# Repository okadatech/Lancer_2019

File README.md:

# Lancer_2019
第22回ロボットグランプリ ランサー部門の機体データ

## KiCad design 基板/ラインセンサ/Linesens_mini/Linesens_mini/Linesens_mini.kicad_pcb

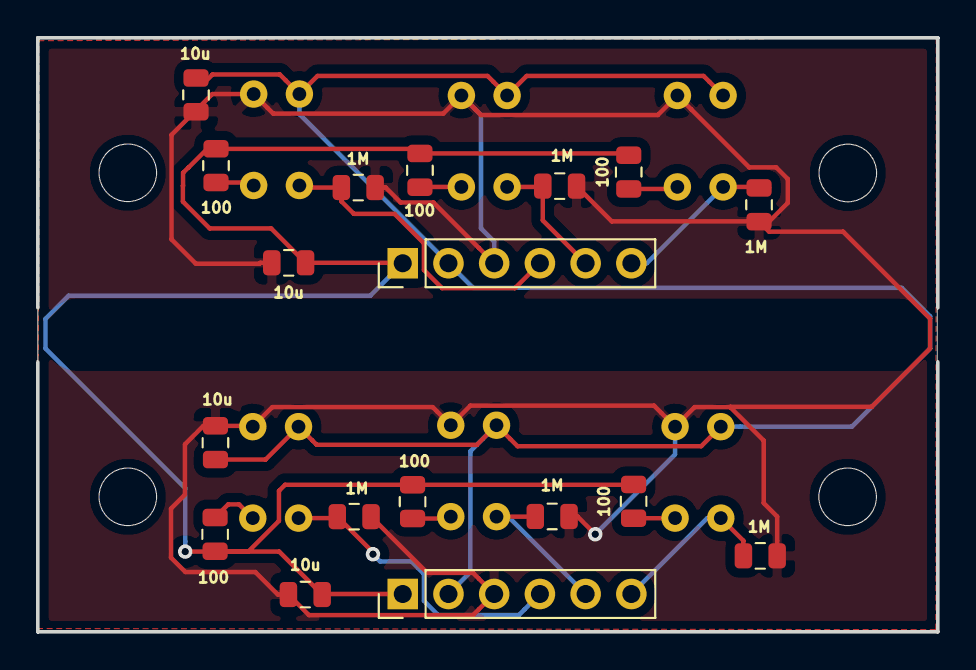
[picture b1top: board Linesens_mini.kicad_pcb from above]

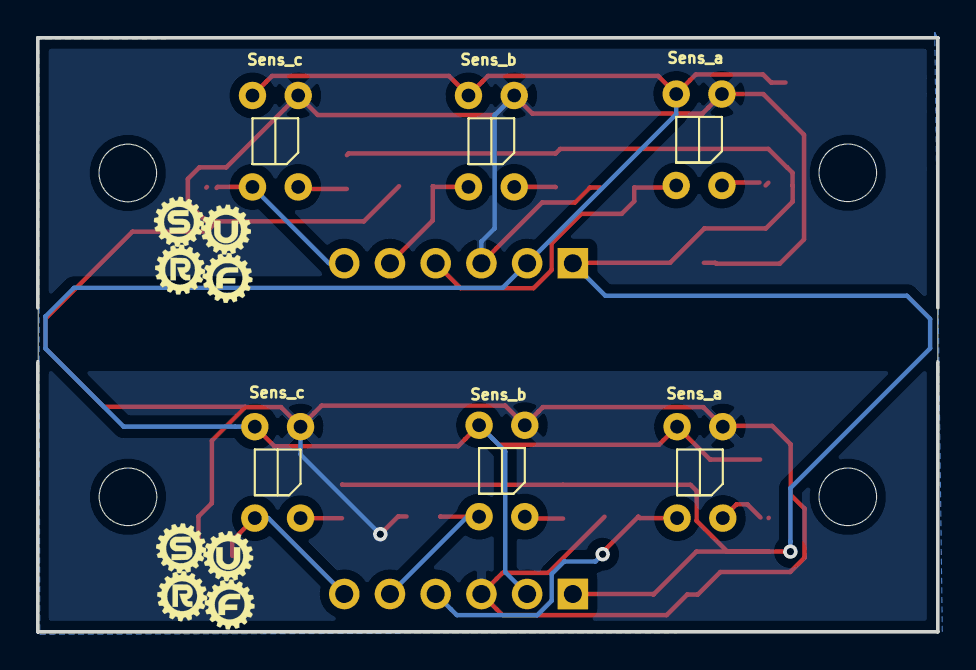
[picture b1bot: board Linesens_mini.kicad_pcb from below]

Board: 2 copper layers, 50.0 x 33.0 mm, 28 parts (6 on the bottom side), 15 nets.

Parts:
10u: 10u; C_0805_2012Metric
 : MountingHole_3.2mm_M3
 #2,  #3,  #6: MountingHole_3.2mm_M3
 #4,  #5: PinHeader_1x06_P2.54mm_Vertical
C1, C2, C4: 10u; C_0805_2012Metric
R1, R3, R5, R7, R9, R11: 100; R_0805_2012Metric
R2, R4, R6, R8, R10, R12: 1M; R_0805_2012Metric
Sens_a: TPR-105F
Sens_a#2: TPR-105F
Sens_b: TPR-105F
Sens_b#2: TPR-105F
Sens_c: TPR-105F
Sens_c#2: TPR-105F

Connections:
+3V3: #4.2, #5.2, C2.1, C4.1, Sens_a.3, Sens_a#2.3, Sens_b.3, Sens_b#2.3, Sens_c.3, Sens_c#2.3
+5V: 10u.1, #4.1, #5.1, C1.1, R1.1, R3.1, R5.1, R7.1, R9.1, R11.1
/Line_out_1: #4.6, R2.1, Sens_c.4
/Line_out_2: #4.5, R4.1, Sens_b.4
/Line_out_3: #4.4, R6.1, Sens_a#2.4
/Line_out_4: #5.6, R8.1, Sens_c#2.4
/Line_out_5: #5.5, R10.1, Sens_b#2.4
/Line_out_6: #5.4, R12.1, Sens_a.4
GND: 10u.2, #4.3, #5.3, C1.2, C2.2, C4.2, R2.2, R4.2, R6.2, R8.2, R10.2, R12.2, Sens_a.2, Sens_a#2.2, Sens_b.2, Sens_b#2.2, Sens_c.2, Sens_c#2.2
unnamed: R1.2, Sens_c.1
unnamed: R3.2, Sens_b.1
unnamed: R5.2, Sens_a#2.1
unnamed: R7.2, Sens_c#2.1
unnamed: R9.2, Sens_b#2.1
unnamed: R11.2, Sens_a.1

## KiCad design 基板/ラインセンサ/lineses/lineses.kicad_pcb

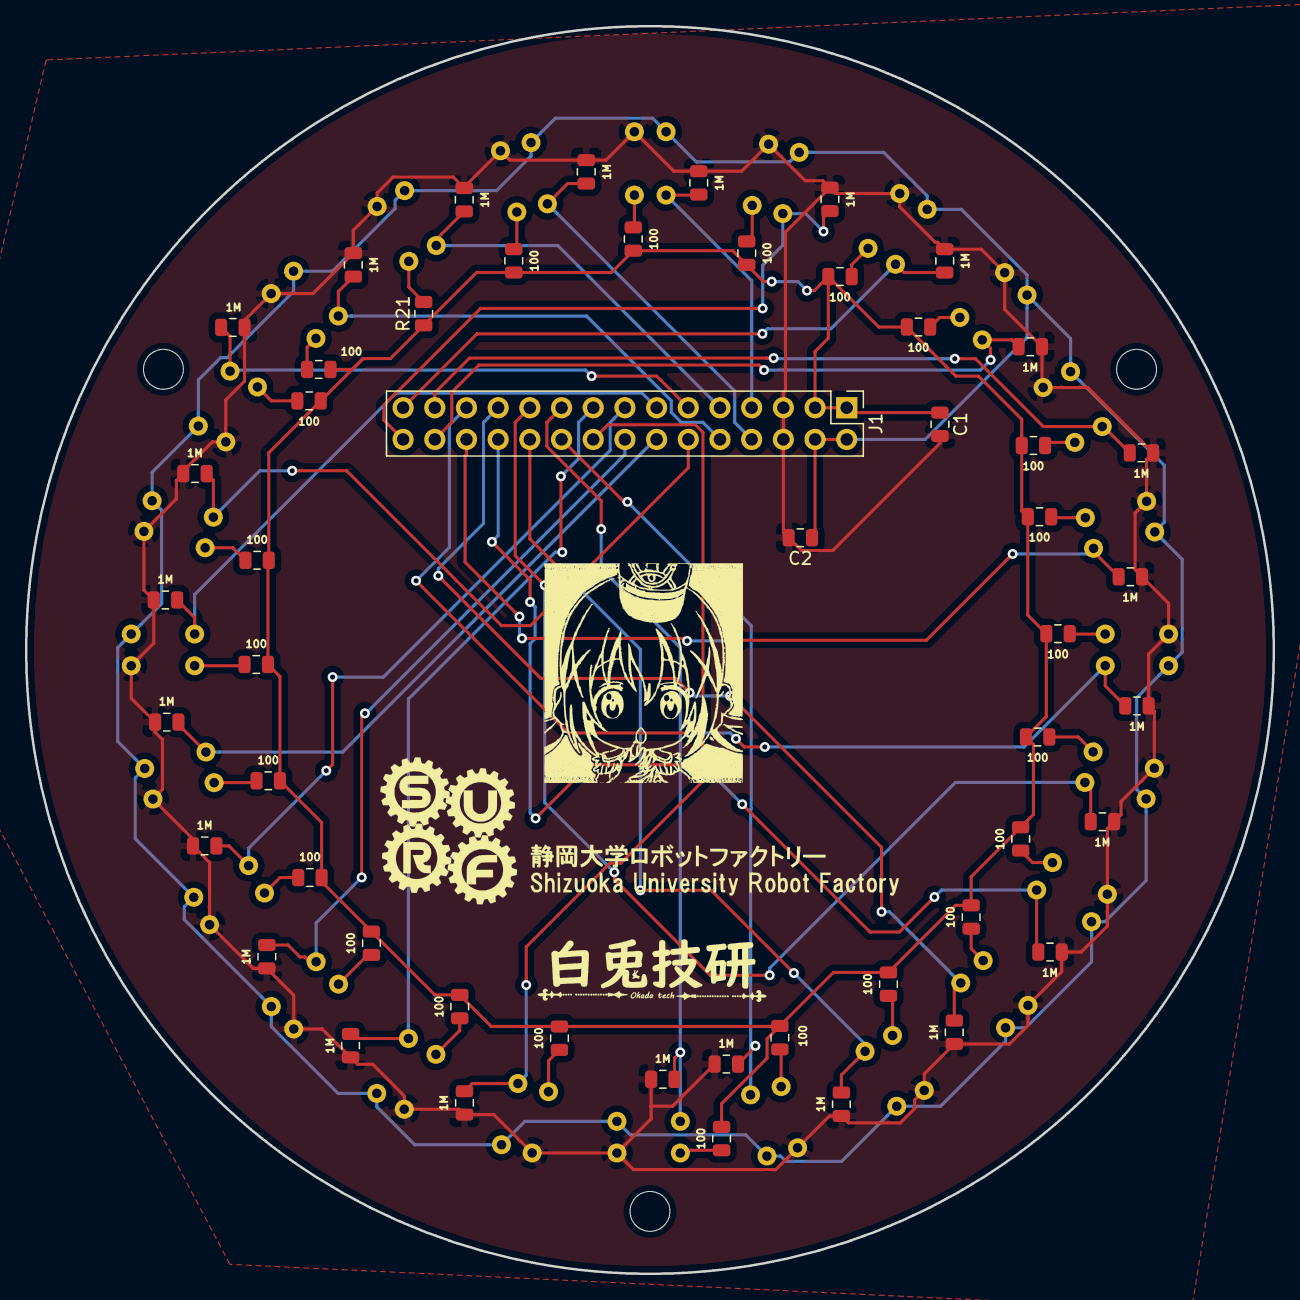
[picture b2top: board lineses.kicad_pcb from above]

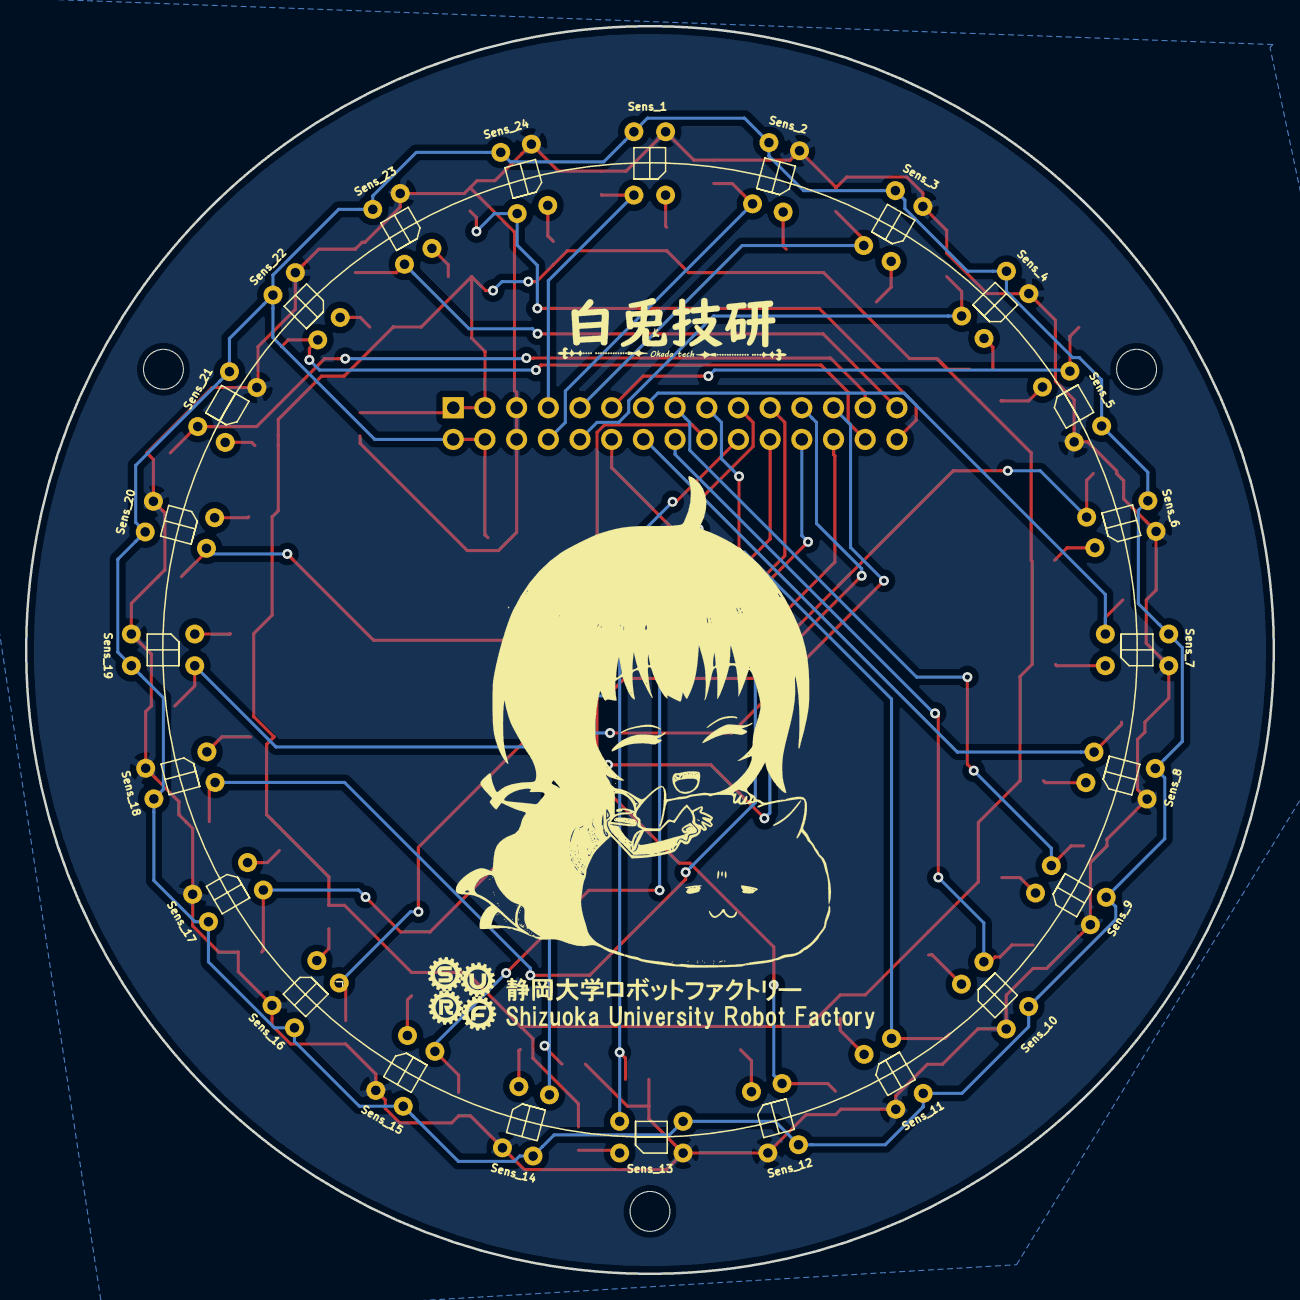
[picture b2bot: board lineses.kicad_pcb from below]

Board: 2 copper layers, 100.0 x 100.0 mm, 85 parts (31 on the bottom side), 51 nets.

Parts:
100: 100; R_0805_2012Metric
 : sirousagikenn
 #2,  #3,  #4: MountingHole_3.2mm_M3
 #5: maya
 #6: SURF_10mm
 #7,  #10: LOGO
 #8: sirousagikenn
 #9: SURF
C1, C2: 10u; C_0805_2012Metric
J1: PinHeader_2x15_P2.54mm_Vertical
R, R2, R7, R9, R10, R16, R17, R18, R20, R26, R27, R28, R29, R36, R37, R39, R45, R46, R48, R52, R53, R54, R58, R60: 1M; R_0805_2012Metric
R1, R3, R5, R6, R11, R12, R13, R15, R21, R22, R23, R24, R31, R32, R34, R42, R44, R49, R50, R51, R55, R56, R57: 100; R_0805_2012Metric
Sens_1, Sens_2, Sens_3, Sens_4, Sens_6, Sens_7, Sens_8, Sens_9, Sens_10, Sens_11, Sens_12, Sens_13, Sens_14, Sens_15, Sens_16, Sens_17, Sens_18, Sens_19, Sens_20, Sens_21, Sens_22, Sens_23, Sens_24: CNY70; TPR-105F
Sens_5: TPR-105F

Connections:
+3V3: C2.1, J1.2, J1.4, Sens_1.3, Sens_2.3, Sens_3.3, Sens_4.3, Sens_5.3, Sens_6.3, Sens_7.3, Sens_8.3, Sens_9.3, Sens_10.3, Sens_11.3, Sens_12.3, Sens_13.3, Sens_14.3, Sens_15.3, Sens_16.3, Sens_17.3, Sens_18.3, Sens_19.3, Sens_20.3, Sens_21.3, Sens_22.3, Sens_23.3, Sens_24.3
+5V: 100.1, C1.1, J1.1, J1.3, R1.1, R3.1, R5.1, R6.1, R11.1, R12.1, R13.1, R15.1, R21.1, R22.1, R23.1, R24.1, R31.1, R32.1, R34.1, R42.1, R44.1, R49.1, R50.1, R51.1, R55.1, R56.1, R57.1
/Line_out_1: J1.7, R2.1, Sens_1.4
/Line_out_2: J1.8, R16.1, Sens_2.4
/Line_out_3: J1.9, R26.1, Sens_3.4
/Line_out_4: J1.10, R36.1, Sens_4.4
/Line_out_5: J1.11, R45.1, Sens_5.4
/Line_out_6: J1.12, R52.1, Sens_6.4
/Line_out_7: J1.13, R58.1, Sens_7.4
/Line_out_8: J1.14, R7.1, Sens_8.4
/Line_out_9: J1.15, R17.1, Sens_9.4
/Line_out_10: J1.16, R27.1, Sens_10.4
/Line_out_11: J1.17, R37.1, Sens_11.4
/Line_out_12: J1.18, R46.1, Sens_12.4
/Line_out_13: J1.19, R53.1, Sens_13.4
/Line_out_14: J1.20, R.1, Sens_14.4
/Line_out_15: J1.21, R10.1, Sens_18.4
/Line_out_16: J1.22, R20.1, Sens_15.4
/Line_out_17: J1.23, R29.1, Sens_16.4
/Line_out_18: J1.24, R39.1, Sens_17.4
/Line_out_19: J1.25, R48.1, Sens_19.4
/Line_out_20: J1.26, R54.1, Sens_20.4
/Line_out_21: J1.27, R60.1, Sens_21.4
/Line_out_22: J1.28, R9.1, Sens_22.4
/Line_out_23: J1.29, R18.1, Sens_23.4
/Line_out_24: J1.30, R28.1, Sens_24.4
GND: C1.2, C2.2, J1.5, J1.6, R.2, R2.2, R7.2, R9.2, R10.2, R16.2, R17.2, R18.2, R20.2, R26.2, R27.2, R28.2, R29.2, R36.2, R37.2, R39.2, R45.2, R46.2, R48.2, R52.2, R53.2, R54.2, R58.2, R60.2, Sens_1.2, Sens_2.2, Sens_3.2, Sens_4.2, Sens_5.2, Sens_6.2, Sens_7.2, Sens_8.2, Sens_9.2, Sens_10.2, Sens_11.2, Sens_12.2, Sens_13.2, Sens_14.2, Sens_15.2, Sens_16.2, Sens_17.2, Sens_18.2, Sens_19.2, Sens_20.2, Sens_21.2, Sens_22.2, Sens_23.2, Sens_24.2
unnamed: R1.2, Sens_1.1
unnamed: R3.2, Sens_8.1
unnamed: R5.2, Sens_22.1
unnamed: R6.2, Sens_18.1
unnamed: R11.2, Sens_2.1
unnamed: R12.2, Sens_9.1
unnamed: R13.2, Sens_23.1
unnamed: R15.2, Sens_15.1
unnamed: R21.2, Sens_3.1
unnamed: R22.2, Sens_10.1
unnamed: R23.2, Sens_24.1
unnamed: R24.2, Sens_16.1
unnamed: R31.2, Sens_4.1
unnamed: R32.2, Sens_11.1
unnamed: R34.2, Sens_17.1
unnamed: 100.2, Sens_5.1
unnamed: R42.2, Sens_12.1
unnamed: R44.2, Sens_19.1
unnamed: R49.2, Sens_6.1
unnamed: R50.2, Sens_13.1
unnamed: R51.2, Sens_20.1
unnamed: R55.2, Sens_7.1
unnamed: R56.2, Sens_14.1
unnamed: R57.2, Sens_21.1

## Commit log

2019-03-18 1st commit
2019-03-18 add openMV script
2019-03-23 会場での調整後
